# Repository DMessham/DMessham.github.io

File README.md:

# Dmessham.github.io
This is my github page used as a landing page, and for hosting my publicaly available content

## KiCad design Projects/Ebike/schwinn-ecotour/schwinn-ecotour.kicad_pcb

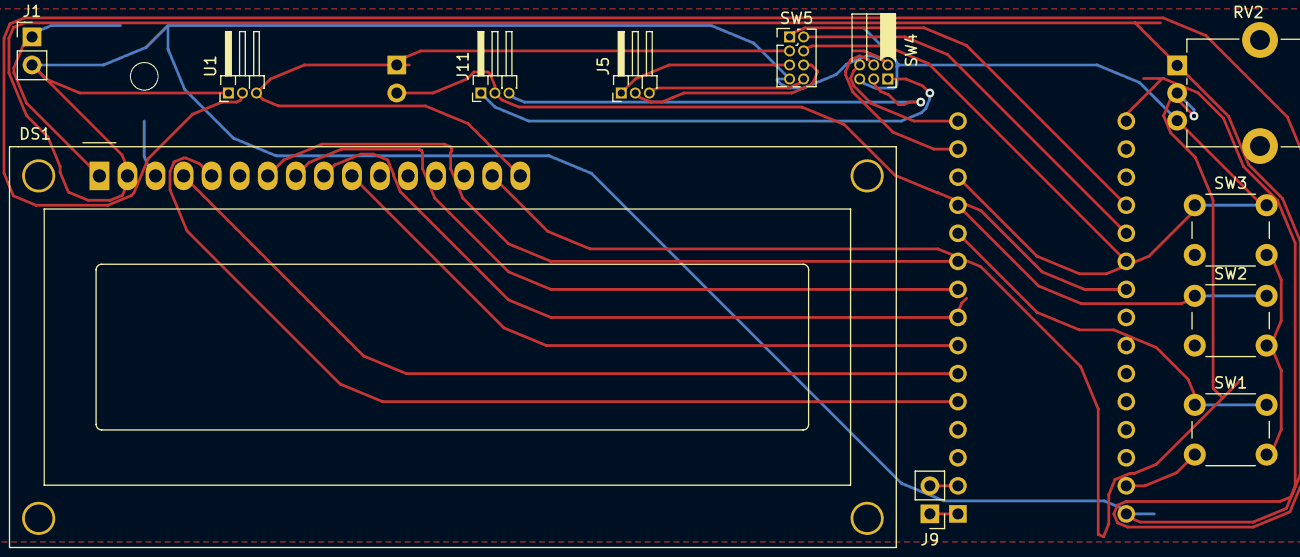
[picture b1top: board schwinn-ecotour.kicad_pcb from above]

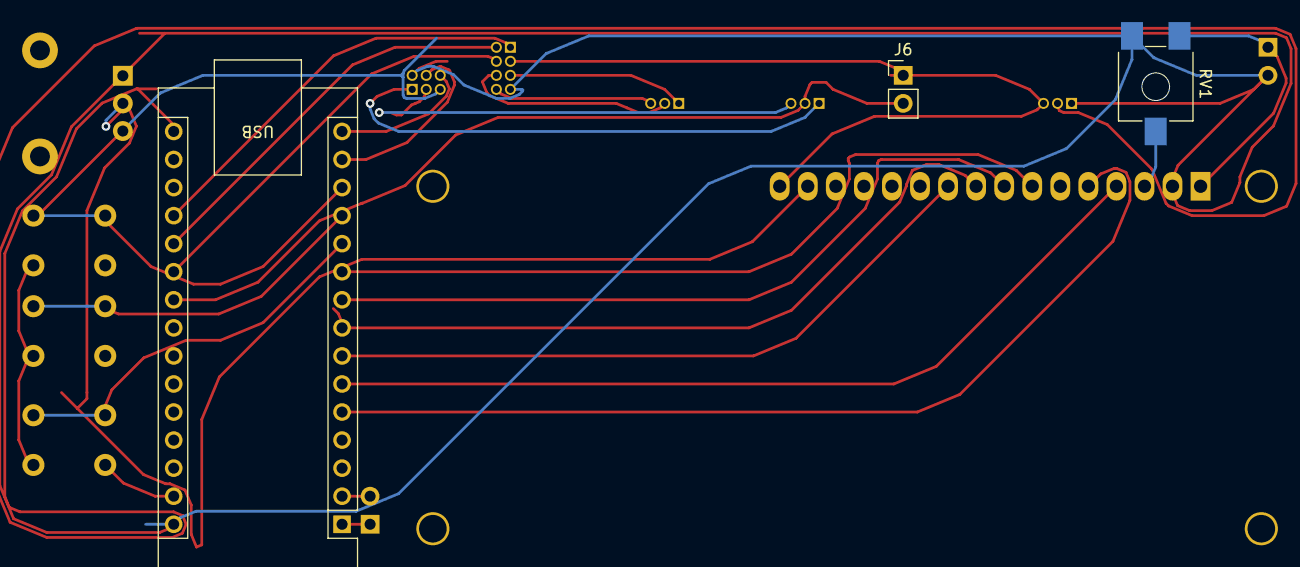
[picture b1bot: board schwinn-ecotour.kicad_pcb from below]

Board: 2 copper layers, 15 parts (3 on the bottom side), 27 nets.

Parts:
A1: Arduino_Nano
DS1: WC1602A
J1: 5vin; PinHeader_1x02_P2.54mm_Vertical
J5: headlight; PinHeader_1x03_P1.27mm_Horizontal
J6: brakesw; PinHeader_1x02_P2.54mm_Vertical
J9: serial; PinHeader_1x02_P2.54mm_Vertical
J11: misclights; PinHeader_1x03_P1.27mm_Horizontal
RV1: contrast; Potentiometer_ACP_CA6-VSMD_Vertical_Hole
RV2: brightness; Potentiometer_Alpha_RD901F-40-00D_Single_Vertical_CircularH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
SW1: Up / +; SW_PUSH_6mm_H4.3mm
SW2: Down / -; SW_PUSH_6mm_H4.3mm
SW3: Enter; SW_PUSH_6mm_H4.3mm
SW4: turn signals; PinSocket_2x03_P1.27mm_Horizontal
SW5: headlights; PinHeader_2x04_P1.27mm_Vertical
U1: SM351LT; PinHeader_1x03_P1.27mm_Horizontal

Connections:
-5V: A1.30 (VIN), DS1.2 (VDD), J1.2, RV1.1, RV2.1, SW4.2 (B), SW5.7, U1.1 (VCC)
GND: A1.29 (GND), DS1.1 (VSS), DS1.16 (LED(-)), J1.1, J6.1, RV1.3, RV2.3, SW1.2, SW2.2, SW3.2, SW4.5 (B), SW5.3, U1.3 (GND)
unnamed: A1.19 (A0), SW5.1
unnamed: A1.20 (A1), SW5.2
unnamed: A1.21 (A2), SW5.4
unnamed: A1.22 (A3), J6.2, J11.2
unnamed: A1.2 (D0/RX), J9.2
unnamed: A1.1 (D1/TX), J9.1
unnamed: A1.5 (D2), DS1.6 (E)
unnamed: A1.6 (D3), DS1.4 (RS)
unnamed: A1.7 (D4), DS1.11 (D4)
unnamed: A1.8 (D5), DS1.12 (D5)
unnamed: A1.9 (D6), DS1.13 (D6)
unnamed: A1.10 (D7), DS1.14 (D7)
unnamed: A1.11 (D8), SW1.1
unnamed: A1.12 (D9), SW2.1
unnamed: A1.13 (D10), SW3.1
unnamed: A1.14 (D11), SW4.4 (A)
unnamed: A1.15 (D12), SW4.6 (C)
unnamed: A1.16 (D13), U1.2 (OUTPUT)
unnamed: DS1.15 (LED(+)), RV2.2
unnamed: DS1.3 (VO), RV1.2
unnamed: J5.1, SW5.5
unnamed: J5.2, SW5.6
unnamed: J5.3, SW5.8
unnamed: J11.1, SW4.1 (A)
unnamed: J11.3, SW4.3 (C)

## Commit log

2021-09-24 Add P5JS Template
2021-09-24 updated template
2021-09-24 Added pong
2021-09-24 attempted to fix unfair ai on pong
2021-09-24 tried to fix fps counter
2021-09-24 Pong: unhooked ball speed from framerate, still havent been able to fix the ai
2021-09-24 Pong; increased ball speed, temporary fix for the ai
2021-09-24 Pong: removed deltaTime based ball speed adjustment due to major bugs
2021-09-24 Pong: teporarily removed bg effects for better performence, reimplemented old ai with slightly less bugs
2021-09-27 added DVDbounce & redflash, changed pong ai again
2021-09-27 Made imported pong and redflash editable in vsCode
2021-09-27 fixxed minor bugs in dvd bounce
2021-09-27 began optimizations on dvd bounce
2021-09-27 fixed DVD framerate and collision issues
2021-09-27 further fixes w/ pong, added page titles
2021-09-27 DVD: tweaked image and movement to improve performance
2021-09-27 DVD: tried to fix some of the floating point weirdness
    the only time you should get weird floating point shenanigans should be from the click to change speed
2021-09-28 ported performence improvements from dvd to pong
2021-09-28 changed pong fps cap from 30 to 60
2021-09-29 added linePerspective, Trafficlight
2021-09-29 fixed traffic light
2021-09-29 tweaked traffic light
2021-09-30 added html based homepage
2021-09-30 fixing some html stuff
2021-09-30 Redid HTML
2021-10-01 Reworked html again
2021-10-01 added favicon
2021-10-01 updated favicon, and css
2021-10-01 more css updates
2021-10-04 added bubble demo, polished up pong
    pong:
    added difficulty settings for ai
    added ability to turn off pong autoplay
    refactored variables for objects into arrays
    made the ball speed increase with time
2021-10-04 fixed ball speed multiplier not being accounted for in bounce physics
2021-10-04 Pong: some more ai tweaks, some minor physics changes
    WHY WONT THE AI WORK PROPERLY
2021-10-04 fixed control bugs
2021-10-05 Pong: Added some amount of polish, temporarily disabled buggy features, added player control info onscreen
2021-10-05 UI tweaks
2021-10-05 more minor ui changes for pong
2021-10-05 some more polish for pong and dvd
2021-10-05 added beginnigs of a dungeon crawler type game
2021-10-07 added perlinTerrain, optimized DVD
2021-10-08 added 2Darray demo as dungeonCrawl, ballarray added
2021-10-12 added mouse control to dungeonCrawl
2021-10-13 gridDemo: added click to scream
2021-10-14 start conway, seperate griddemo from dungeoncrawl
2021-10-15 conway mostly done, just needs save/load and polish
2021-10-18 changed save/load on conway, added gridCharecter
2021-10-19 Readded index.html, style.css, improved dungeon crawl
2021-10-25 updated dungeoncrawl: added images, worked on level1
2021-10-26 DungeonCrawl: fixed last position replacement
    going over non grass tiles no longer replaces tiles with grass
2021-10-27 addded reversi
2021-10-27 added OOP Walker demo
2021-10-27 implemented OOp walker, ported mouse cursor code from sudoku to DungeonCrawler and Reversi, added some missing links to index.html
2021-11-01 added oopBall, added Paint2d
2021-11-02 added fireworks demo, started work on minesweeper,
2021-11-03 Significant updates to mine,
    ADDED:
    rng based map
    added win and lose conditions that work somewhat (win is broken rn)
    PLACEHOLDERS:
    added placeholder for "paint bucket" style fill of empty areas
    added broken nearby mine number to discovered areas
2021-11-04 added oop timer, more changes to minesweeper
    added better rng infrastructure
    broke the number display at some point
    reworked the fill colour system
    removed unused functions and code
    todo
2021-11-06 added oopButton demo, MAjor updates to minesweep
    fixed the rng in minesweep to be <i>not garbage</i>
    removed some redunant Code, and generally improved efficency a bit (its still not great, the fill algorithm is literally an infinite loop)
    added a whole of if variable to track stats and info for ui
    TODO: fix fill so its not a walking memory leak waiting to happen if someone trys to cheat or something
    implement the ui
2021-11-15 reorganization
2021-12-08 triangle demo
2022-01-17 several in class demos, link to cs30 final project
2022-02-26 rework for use as a proper landing page
2022-11-27 Some long overdue, but minor changes
2023-10-12 Forgot to push almost a year worth of changes whoops
2023-10-12 Add start of my personal projects
2023-10-12 add projects folder to homepage
2023-10-13 Add to Ebike project, update about&contact
2023-10-13 minor tweaks to project page
    github pages why wont you work
2023-10-13 organize old projects
2023-10-13 more minor additions to ebike project
2023-10-14 update bike page
2023-10-15 Rework CSS, Updates to all pages, Remove old stuff
2023-10-17 begin kicad designed dashboard
2023-10-17 update pcb layout (forgot to hit save)
2023-10-20 Move to Simulide for arduino prototyping
2023-10-20 more math in arduino code for speedometer
2023-10-21 more arduino work
2023-10-23 more schematic work
2023-10-23 more schematic & pcb work
